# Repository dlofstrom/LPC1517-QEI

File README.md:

# LPC1517-QEI
This repository contains source files for a 3-Axis Gimbal using the NXP LPC1517.

Also there are a code example showing how to interfaces a quadrature encoder on the NXP LPC1517 using LPCXpresso.

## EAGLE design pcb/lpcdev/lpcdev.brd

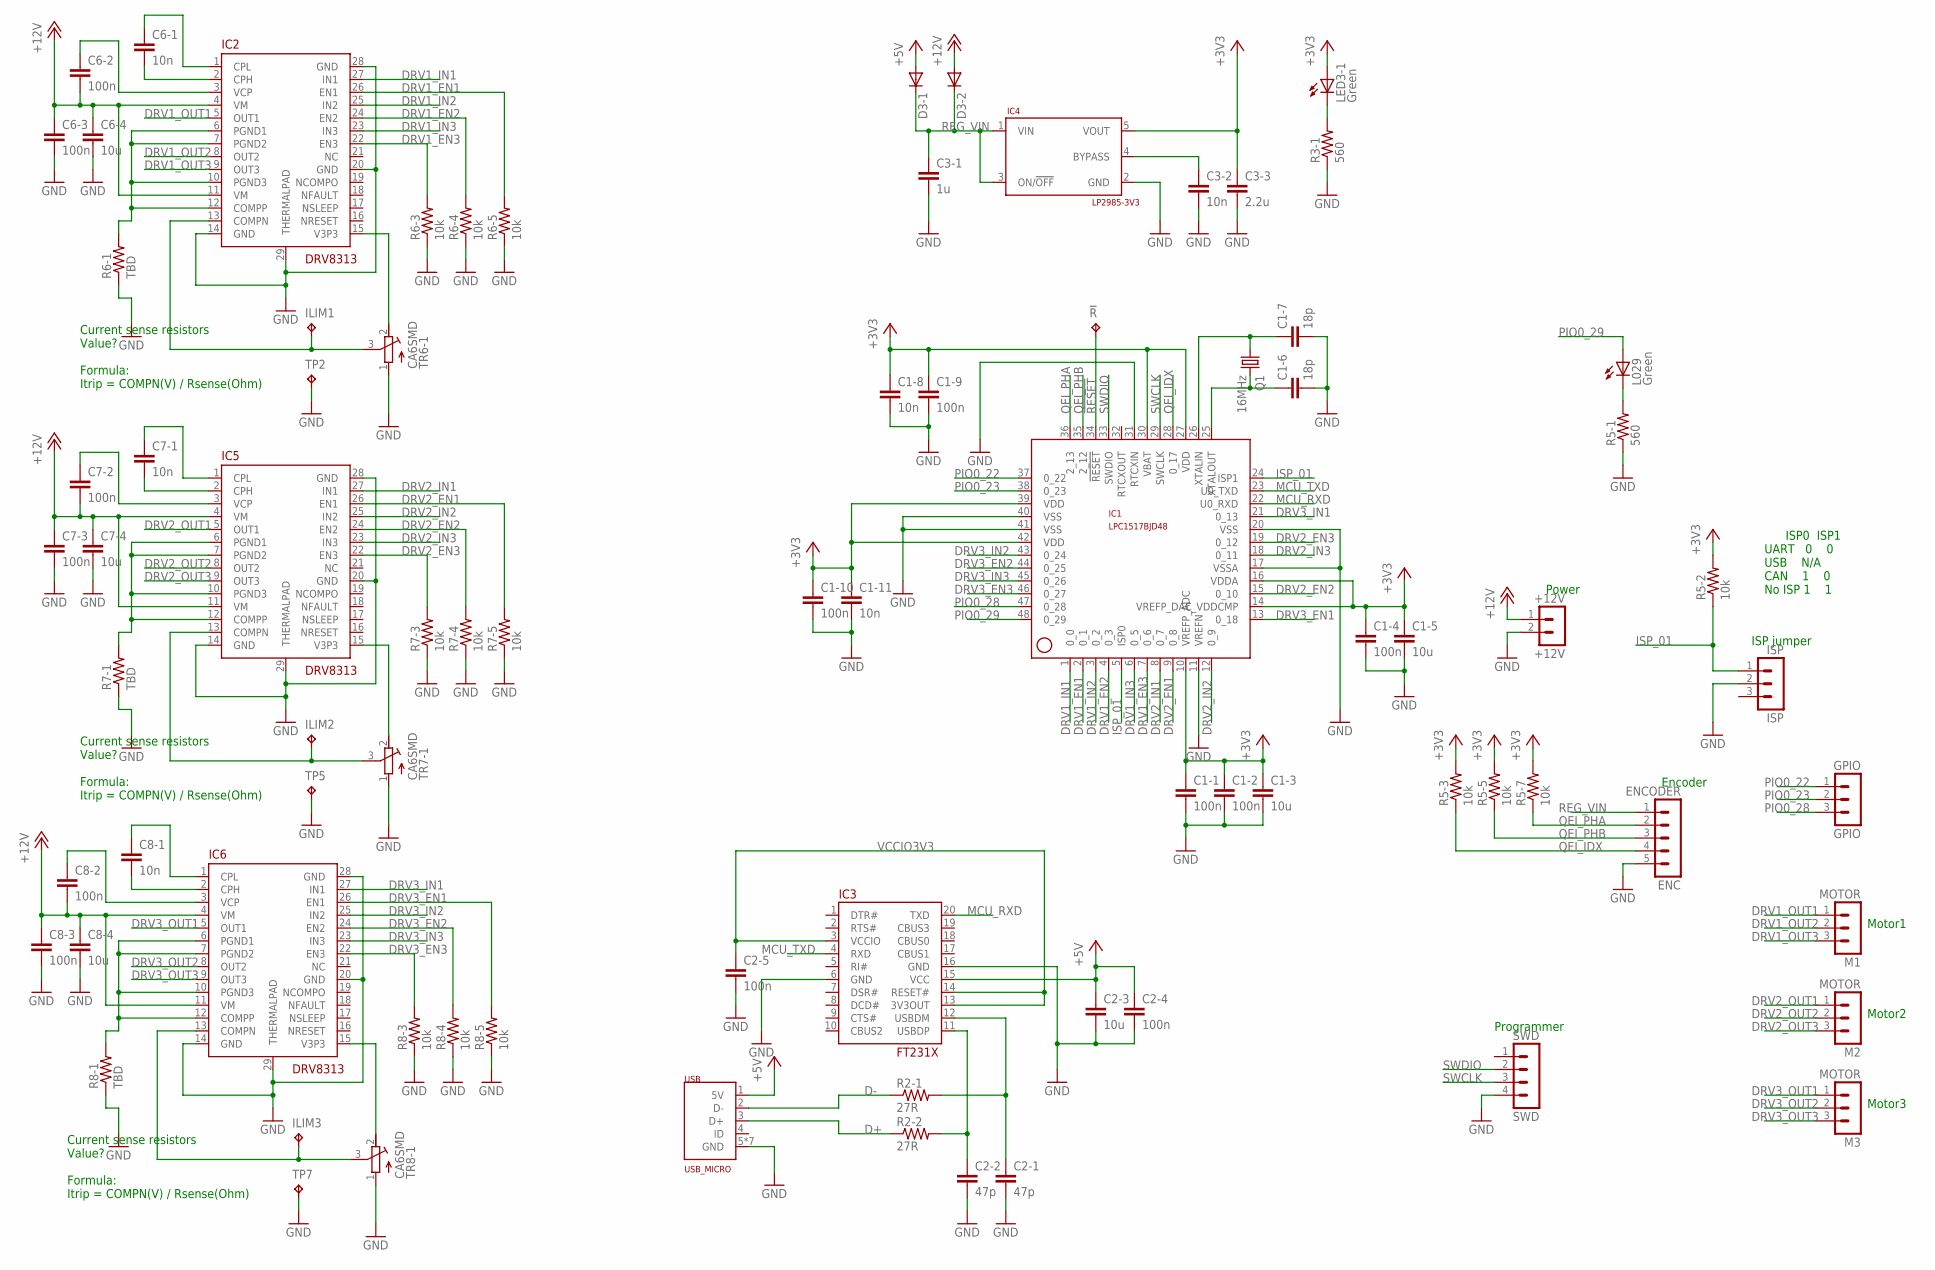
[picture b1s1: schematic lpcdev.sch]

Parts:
!R: TPB1,27; B1,27
+12V: +12V; MA02-1
C1-1, C1-2, C1-4, C1-9, C1-10, C2-4, C2-5, C6-2, C6-3, C7-2, C7-3, C8-2, C8-3: 100n; C0603
C1-3, C1-5, C2-3, C6-4, C7-4, C8-4: 10u; C0805
C1-6, C1-7: 18p; C0603
C1-8, C1-11, C3-2, C6-1, C7-1, C8-1: 10n; C0603
C2-1, C2-2: 47p; C0603
C3-1: 1u; C0805
C3-3: 2.2u; C0805
D3-1, D3-2: DIODE-SOD323-R; SOD323-R
ENC: ENCODER; MA05-1
GPIO: GPIO; MA03-1
IC1: LPC1517BJD48; LQFP48
IC2, IC5, IC6: DRV8313; R-PDSO-G28
IC3: FT231X; SSOP-20
IC4: LP2985-3V3; SOT23
ILIM1, ILIM2, ILIM3: TPB1,27; B1,27
ISP: ISP; MA03-1
L029: Green; CHIP-LED0603
LED3-1: Green; CHIP-LED0603
M1, M2, M3: MOTOR; MA03-1
Q1: 16MHz; CTS406
R2-1, R2-2: 27R; R0603
R3-1, R5-1: 560; R0603
R5-2, R5-3, R5-5, R5-7, R6-3, R6-4, R6-5, R7-3, R7-4, R7-5, R8-3, R8-4, R8-5: 10k; R0603
R6-1, R7-1, R8-1: TBD; R0805
SWD: SWD; MA04-1
TP2, TP5, TP7: TPB1,27; B1,27
TR6-1, TR7-1, TR8-1: CA6SMD
USB: USB_MICRO

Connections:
!RESET: !R.TP, IC1.34 (!RESET)
+3V3: C1-1.1, C1-2.1, C1-3.1, C1-4.1, C1-5.1, C1-8.1, C1-9.1, C1-10.1, C1-11.1, C3-3.1, IC1.10 (VREFP_ADC), IC1.14 (VREFP_DAC_VDDCMP), IC1.16 (VDDA), IC1.27 (VDD), IC1.30 (VBAT), IC1.39 (VDD), IC1.42 (VDD), IC4.5 (VOUT), LED3-1.A, R5-2.2, R5-3.2, R5-5.2, R5-7.2
+5V: C2-3.1, C2-4.1, D3-1.A, IC3.15 (VCC), USB.1 (5V)
+12V: +12V.1, C6-2.2, C6-3.1, C6-4.1, C7-2.2, C7-3.1, C7-4.1, C8-2.2, C8-3.1, C8-4.1, D3-2.A, IC2.4 (VM), IC2.11 (VM), IC5.4 (VM), IC5.11 (VM), IC6.4 (VM), IC6.11 (VM)
D+: R2-2.1, USB.3 (D+)
D-: R2-1.1, USB.2 (D-)
DRV1_3V3: IC2.15 (V3P3), TR6-1.2 (E)
DRV1_COMPN: IC2.13 (COMPN), ILIM1.TP, TR6-1.3 (S)
DRV1_COMPP: IC2.6 (PGND1), IC2.7 (PGND2), IC2.10 (PGND3), IC2.12 (COMPP), R6-1.2
DRV1_CPH: C6-1.2, IC2.2 (CPH)
DRV1_CPL: C6-1.1, IC2.1 (CPL)
DRV1_EN1: IC1.2 (0_1), IC2.26 (EN1), R6-5.2
DRV1_EN2: IC1.4 (0_3), IC2.24 (EN2), R6-4.2
DRV1_EN3: IC1.7 (0_6), IC2.22 (EN3), R6-3.2
DRV1_IN1: IC1.1 (0_0), IC2.27 (IN1)
DRV1_IN2: IC1.3 (0_2), IC2.25 (IN2)
DRV1_IN3: IC1.6 (0_5), IC2.23 (IN3)
DRV1_OUT1: IC2.5 (OUT1), M1.1
DRV1_OUT2: IC2.8 (OUT2), M1.2
DRV1_OUT3: IC2.9 (OUT3), M1.3
DRV1_VCP: C6-2.1, IC2.3 (VCP)
DRV2_3V1: IC5.15 (V3P3), TR7-1.2 (E)
DRV2_COMPN1: IC5.13 (COMPN), ILIM2.TP, TR7-1.3 (S)
DRV2_COMPP1: IC5.6 (PGND1), IC5.7 (PGND2), IC5.10 (PGND3), IC5.12 (COMPP), R7-1.2
DRV2_CPH1: C7-1.2, IC5.2 (CPH)
DRV2_CPL1: C7-1.1, IC5.1 (CPL)
DRV2_EN1: IC1.9 (0_8), IC5.26 (EN1), R7-5.2
DRV2_EN2: IC1.15 (0_10), IC5.24 (EN2), R7-4.2
DRV2_EN3: IC1.19 (0_12), IC5.22 (EN3), R7-3.2
DRV2_IN1: IC1.8 (0_7), IC5.27 (IN1)
DRV2_IN2: IC1.12 (0_9), IC5.25 (IN2)
DRV2_IN3: IC1.18 (0_11), IC5.23 (IN3)
DRV2_OUT1: IC5.5 (OUT1), M2.1
DRV2_OUT2: IC5.8 (OUT2), M2.2
DRV2_OUT3: IC5.9 (OUT3), M2.3
DRV2_VCP1: C7-2.1, IC5.3 (VCP)
DRV3_3V2: IC6.15 (V3P3), TR8-1.2 (E)
DRV3_COMPN2: IC6.13 (COMPN), ILIM3.TP, TR8-1.3 (S)
DRV3_COMPP2: IC6.6 (PGND1), IC6.7 (PGND2), IC6.10 (PGND3), IC6.12 (COMPP), R8-1.2
DRV3_CPH2: C8-1.2, IC6.2 (CPH)
DRV3_CPL2: C8-1.1, IC6.1 (CPL)
DRV3_EN1: IC1.13 (0_18), IC6.26 (EN1), R8-5.2
DRV3_EN2: IC1.44 (0_25), IC6.24 (EN2), R8-4.2
DRV3_EN3: IC1.46 (0_27), IC6.22 (EN3), R8-3.2
DRV3_IN1: IC1.21 (0_13), IC6.27 (IN1)
DRV3_IN2: IC1.43 (0_24), IC6.25 (IN2)
DRV3_IN3: IC1.45 (0_26), IC6.23 (IN3)
DRV3_OUT1: IC6.5 (OUT1), M3.1
DRV3_OUT2: IC6.8 (OUT2), M3.2
DRV3_OUT3: IC6.9 (OUT3), M3.3
DRV3_VCP2: C8-2.1, IC6.3 (VCP)
GND: +12V.2, C1-1.2, C1-2.2, C1-3.2, C1-4.2, C1-5.2, C1-6.2, C1-7.2, C1-8.2, C1-9.2, C1-10.2, C1-11.2, C2-1.2, C2-2.2, C2-3.2, C2-4.2, C2-5.2, C3-1.2, C3-2.2, C3-3.2, C6-3.2, C6-4.2, C7-3.2, C7-4.2, C8-3.2, C8-4.2, ENC.5, IC1.11 (VREFN), IC1.17 (VSSA), IC1.20 (VSS), IC1.31 (RTCXIN), IC1.40 (VSS), IC1.41 (VSS), IC2.14 (GND), IC2.20 (GND), IC2.28 (GND), IC2.29 (THERMALPAD), IC3.6 (GND), IC3.16 (GND), IC4.2 (GND), IC5.14 (GND), IC5.20 (GND), IC5.28 (GND), IC5.29 (THERMALPAD), IC6.14 (GND), IC6.20 (GND), IC6.28 (GND), IC6.29 (THERMALPAD), ISP.2, R3-1.1, R5-1.1, R6-1.1, R6-3.1, R6-4.1, R6-5.1, R7-1.1, R7-3.1, R7-4.1, R7-5.1, R8-1.1, R8-3.1, R8-4.1, R8-5.1, SWD.4, TP2.TP, TP5.TP, TP7.TP, TR6-1.1 (A), TR7-1.1 (A), TR8-1.1 (A), USB.5 (GND), USB.H1 (GND), USB.H2 (GND), USB.S1 (GND), USB.S2 (GND), USB.S3 (GND), USB.S4 (GND)
ISP_01: IC1.5 (ISP0), IC1.24 (ISP1), ISP.1, R5-2.1
LED1: L029.C, R5-1.2
LED2: LED3-1.C, R3-1.2
MCU_RXD: IC1.22 (U0_RXD), IC3.20 (TXD)
MCU_TXD: IC1.23 (U0_TXD), IC3.4 (RXD)
PIO0_22: GPIO.1, IC1.37 (0_22)
PIO0_23: GPIO.2, IC1.38 (0_23)
PIO0_28: GPIO.3, IC1.47 (0_28)
PIO0_29: IC1.48 (0_29), L029.A
QEI_IDX: ENC.4, IC1.28 (0_17), R5-3.1
QEI_PHA: ENC.2, IC1.36 (2_13), R5-7.1
QEI_PHB: ENC.3, IC1.35 (2_12), R5-5.1
REG_BYPASS: C3-2.1, IC4.4 (BYPASS)
REG_VIN: C3-1.1, D3-1.C, D3-2.C, ENC.1, IC4.1 (VIN), IC4.3 (ON/!OFF)
SWCLK: IC1.29 (SWCLK), SWD.3
SWDIO: IC1.33 (SWDIO), SWD.2
USBDM: C2-1.1, IC3.12 (USBDM), R2-1.2
USBDP: C2-2.1, IC3.11 (USBDP), R2-2.2
VCCIO3V3: C2-5.1, IC3.3 (VCCIO), IC3.13 (3V3OUT), IC3.14 (RESET#)
XTALIN: C1-7.1, IC1.26 (XTALIN), Q1.1
XTALOUT: C1-6.1, IC1.25 (XTALOUT), Q1.3 (2)

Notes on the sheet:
ISP0 ISP1 UART 0 0 USB N/A CAN 1 0 No ISP 1 1
ISP jumper
Encoder
Motor3
Current sense resistors Value? Formula: Itrip = COMPN(V) / Rsense(Ohm)
Programmer
Power
Motor1
Motor2

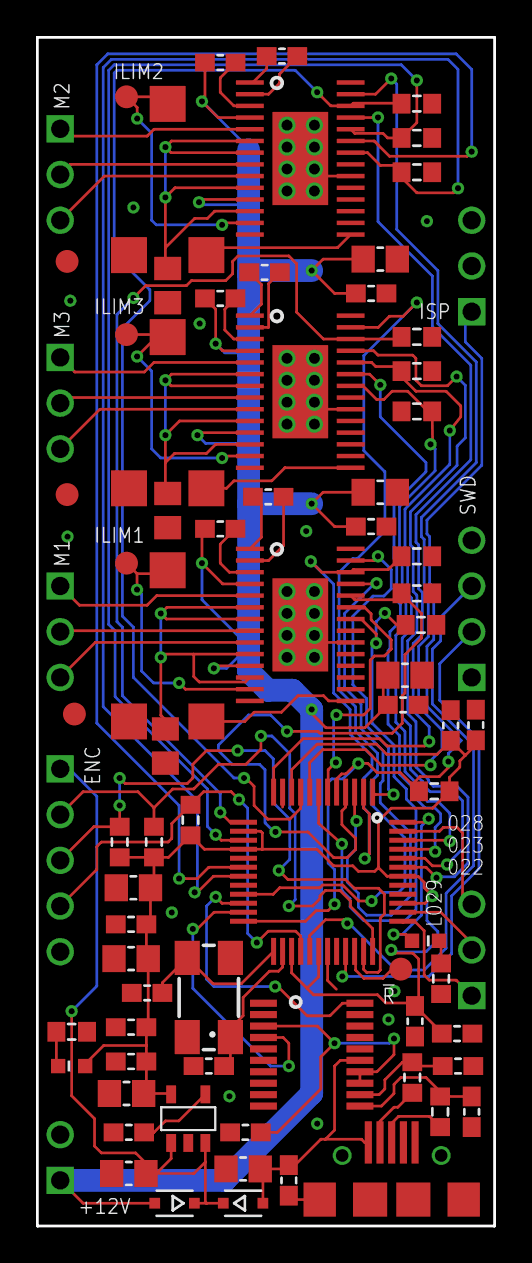
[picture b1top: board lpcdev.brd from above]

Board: 2 copper layers, 25.4 x 66.0 mm, 81 parts (0 on the bottom side), 73 nets.

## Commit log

2016-03-31 Serial printout working example
2016-09-29 First working example
2016-09-29 Modified Readme
2016-10-05 Schematic for development board
2016-10-07 Added two more motor drivers, named nets and made first pass on board placement
2016-10-08 rough routing (no gnd)
2016-10-15 Routing complete, ERC and DRC is OK
2016-10-18 final touchup and gerber generating
2017-02-09 Assembly instructions added
